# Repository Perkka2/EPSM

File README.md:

# EPSM
 NES Expansion Port Sound Module (Earlier: Expansion Port Sound Generator)

### An expansion sound card for the Nintendo Entertainment System

It uses an Yamaha YMF288 Soundchip that gives a lot of new audio capabilities to the NES.

## Features of YMF288:
* 3 Pulse Channels with Envelope and Noise
* 6 4OP FM Channels with hard panning stereo.
* 6 Rythm channels featuring 6 different ADPCM Drum Recordings with Hard Panning Stereo support
* 2 Timed IRQ's
## Added features of the EPSM
* Forwards expansion audio from supported gamecarts
  * Original Famicom expansion audio games with compatible adapter
  * PowerPak
  * EverDrive N8
  * EverDrive N8 Pro
  * Other carts using EXP2, EXP6 or EXP9 to output audio
* Alternative 3.5mm jack for Stereo output
  * EPSM Audio forwarding to the NES RCA/RF outputs are disabled when the 3.5mm jack is plugged in
  * NES Audio and Cart Expansion audio plays as Dual Mono on the 3.5mm jack.

## Tools
* Mesen-X: Supports playback of EPSM using any mapper.
* FamiStudio: Allows for music creation for the EPSM and has both ROM and NSF export options.

## Usage
* [Addressing](Docs/Addressing.md)
* [Addressing Fiskbit's Fallback Handler](Docs/Fiskbit-FallbackHandler.md)
* [NESDev wiki](https://www.nesdev.org/wiki/Expansion_Port_Sound_Module)
* [N8 Pro Mappers with EPSM Addressing](Files/N8ProEPSM.zip)

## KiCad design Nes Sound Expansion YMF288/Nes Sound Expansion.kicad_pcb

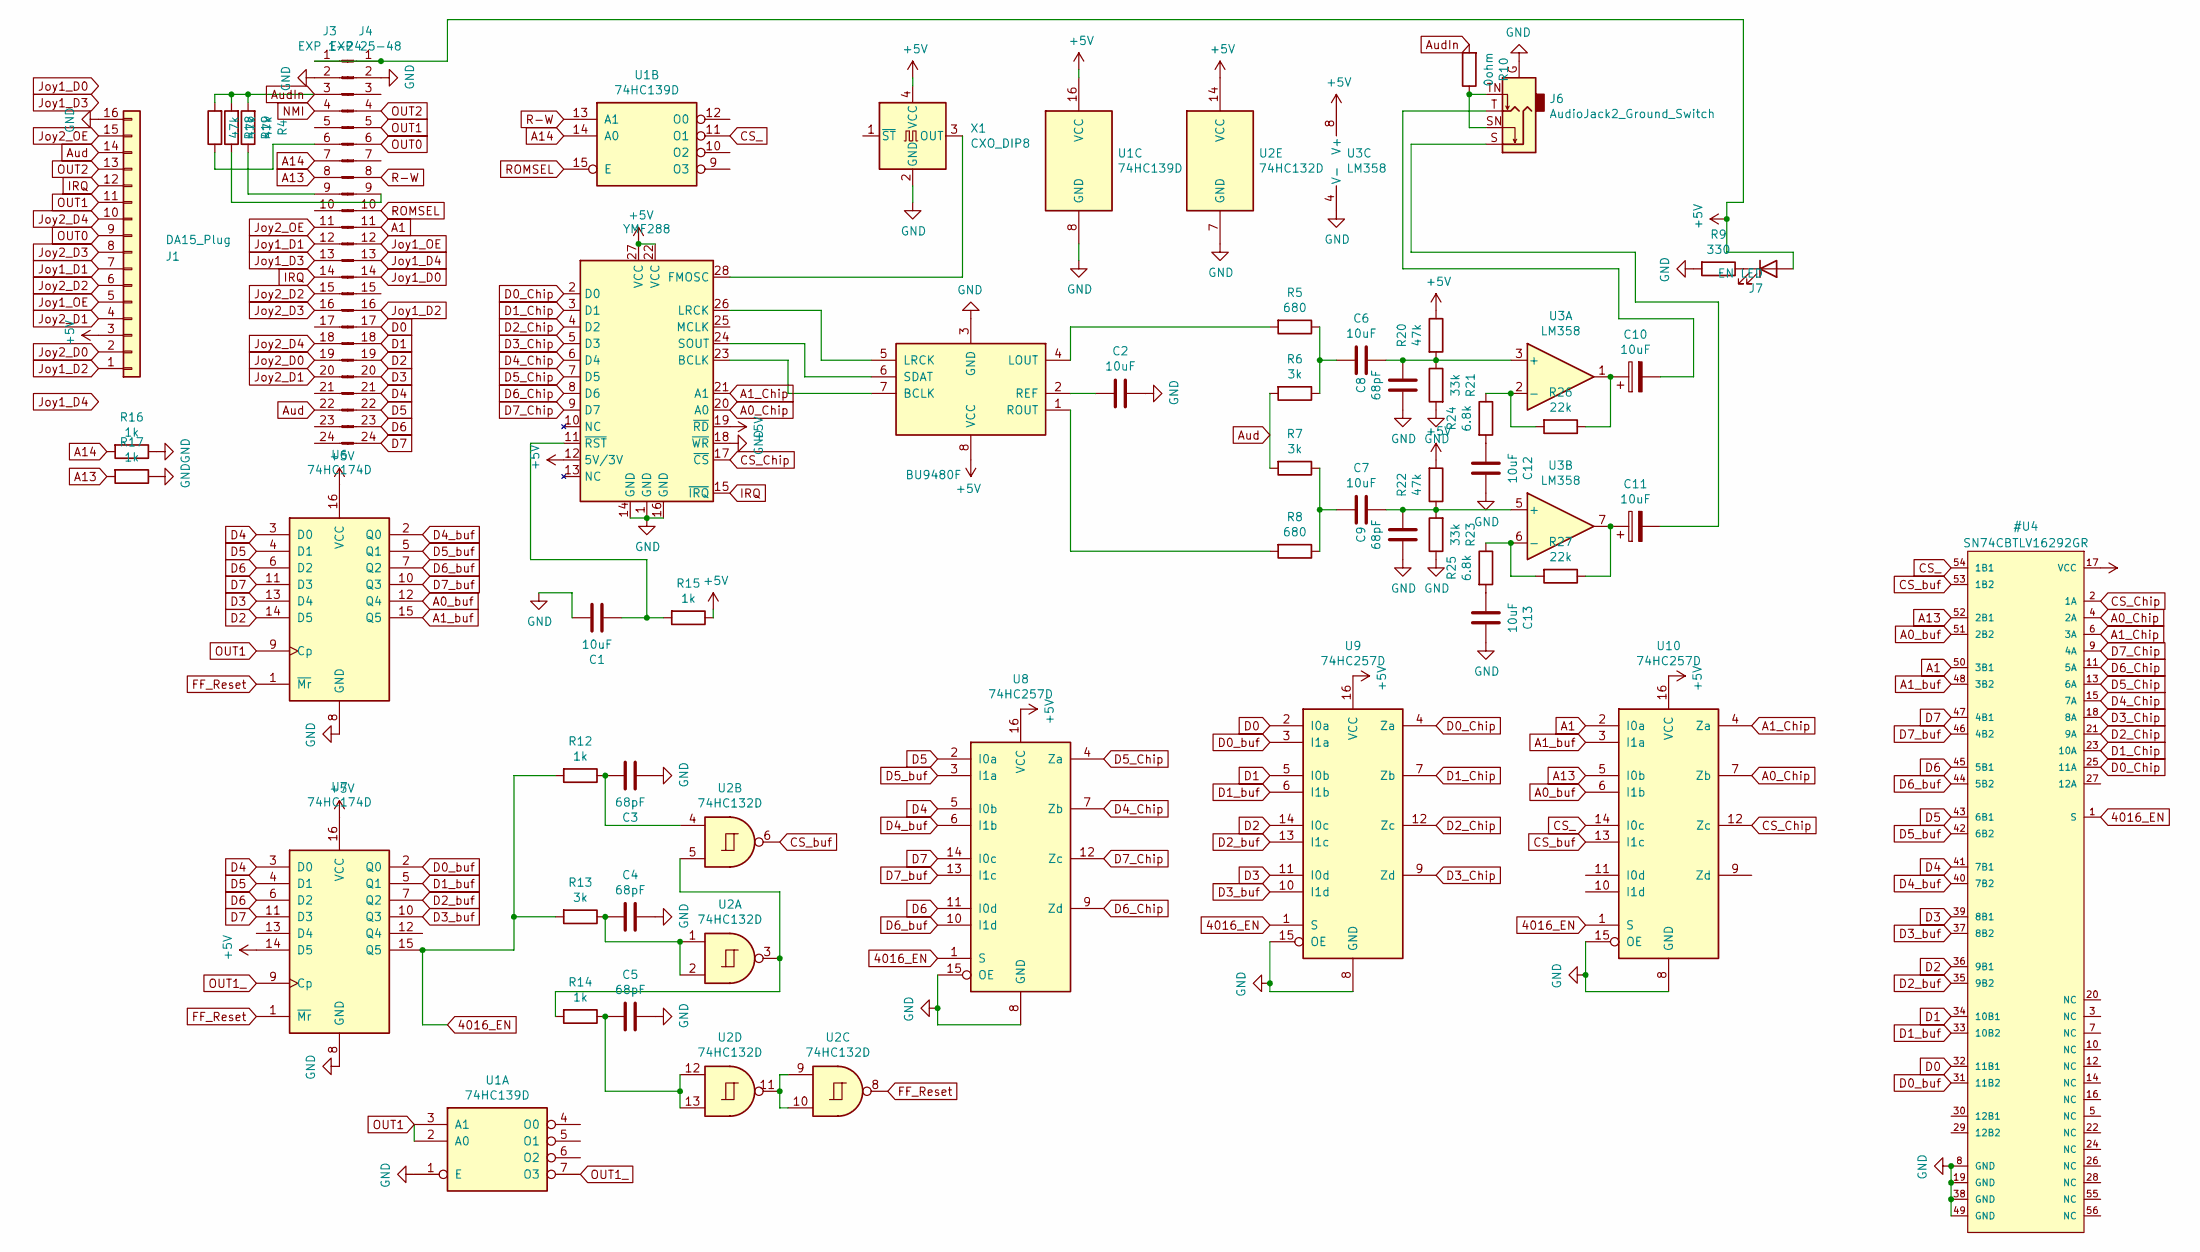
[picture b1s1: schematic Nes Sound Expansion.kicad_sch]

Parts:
BU9480F1: BU9480F; SOIC-8_3.9x4.9mm_P1.27mm
C1, C2, C6, C7, C12, C13: 10uF; C_0805_2012Metric
C3, C4, C5, C8, C9: 68pF; C_0603_1608Metric
C10, C11: 10uF; CP_Elec_4x5.3
J1: DA15_Plug; IDC-Header_2x08_P2.54mm_Vertical
J3: EXP 1-24; PinHeader_1x24_P2.54mm_Vertical
J4: EXP 25-48; PinHeader_1x24_P2.54mm_Vertical
J6: AudioJack2_Ground_Switch; Jack_3.5mm_PJ311_Horizontal_other_pinout
J7: EN LED; LED_0805_2012Metric
R4, R18, R19, R20, R22: 47k; R_0603_1608Metric
R5, R8: 680; R_0603_1608Metric
R6, R7, R13: 3k; R_0603_1608Metric
R9: 330; R_0603_1608Metric
R10: 0ohm; R_0603_1608Metric
R12, R14, R15, R16, R17: 1k; R_0603_1608Metric
R21, R23: 33k; R_0603_1608Metric
R24, R25: 6.8k; R_0603_1608Metric
R26, R27: 22k; R_0603_1608Metric
U1: 74HC139D; SOIC-16_3.9x9.9mm_P1.27mm
U2: 74HC132D; SOIC-14_3.9x8.7mm_P1.27mm
U3: LM358; SOIC-8_3.9x4.9mm_P1.27mm
U6, U7: 74HC174D; SOIC-16_3.9x9.9mm_P1.27mm
U8, U9, U10: 74HC257D; SOIC-16_3.9x9.9mm_P1.27mm
X1: CXO_DIP8; Oscillator_SMD_SeikoEpson_SG8002LB-4Pin_5.0x3.2mm
YMF288: YMF288

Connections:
A14: J3.7, R16.2, U1.14 (A0)
Aud: J1.14, J3.22, R6.2, R7.2
AudIn: J3.3, R4.2, R10.2, R18.2, R19.2
FF_Reset: U2.8, U6.1 (~Mr), U7.1 (~Mr)
IRQ: J1.12, J3.14, YMF288.15 (~IRQ)
Joy1_D0: J4.14
Joy1_D1: J1.7, J3.12
Joy1_D2: J1.1, J4.16
Joy1_D3: J3.13
Joy1_D4: J4.13
Joy1_OE: J1.5, J4.12
Joy2_D0: J1.2, J3.19
Joy2_D1: J1.4, J3.20
Joy2_D2: J1.6, J3.15
Joy2_D3: J1.8, J3.16
Joy2_D4: J1.10, J3.18
Joy2_OE: J1.15, J3.11
NMI: J3.4
unnamed: BU9480F1.7 (BCLK), YMF288.23 (BCLK)
unnamed: BU9480F1.4 (LOUT), R5.2
unnamed: BU9480F1.5 (LRCK), YMF288.26 (LRCK)
unnamed: BU9480F1.2 (REF), C2.1
unnamed: BU9480F1.1 (ROUT), R8.2
unnamed: BU9480F1.6 (SDAT), YMF288.24 (SOUT)
unnamed: C3.2, R12.1, U2.4
unnamed: C4.1, R13.1, U2.1, U2.2
unnamed: C5.1, R14.1, U2.12, U2.13
unnamed: C6.1, R5.1, R6.1
unnamed: C7.1, R7.1, R8.1
unnamed: C10.1, R26.1, U3.1
unnamed: C10.2, J6.T
unnamed: C11.1, R27.1, U3.7
unnamed: C11.2, J6.S
unnamed: C12.1, R24.2
unnamed: C13.1, R25.2
unnamed: J3.6, R18.1
unnamed: J3.9, R4.1
unnamed: J4.9, R19.1
unnamed: J6.SN, J6.TN, R10.1
unnamed: J7.1 (K), R9.1
unnamed: R14.2, U2.3, U2.5
unnamed: U2.9, U2.10, U2.11
unnamed: C6.2, C8.1, R20.2, R21.1, U3.3 (+)
unnamed: R24.1, R26.2, U3.2 (-)
unnamed: C7.2, C9.2, R22.1, R23.2, U3.5 (+)
unnamed: R25.1, R27.2, U3.6 (-)
unnamed: X1.3 (OUT), YMF288.28 (FMOSC)
unnamed: C1.1, R15.2, YMF288.11 (~RST)
OUT0: J1.9, J4.6
OUT1: J1.11, J4.5, U1.2 (A0), U1.3 (A1), U6.9 (Cp)
OUT1_: U1.7 (O3), U7.9 (Cp)
OUT2: J1.13, J4.4
R-W: J4.8, U1.13 (A1)
ROMSEL: J4.10, U1.15 (E)

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
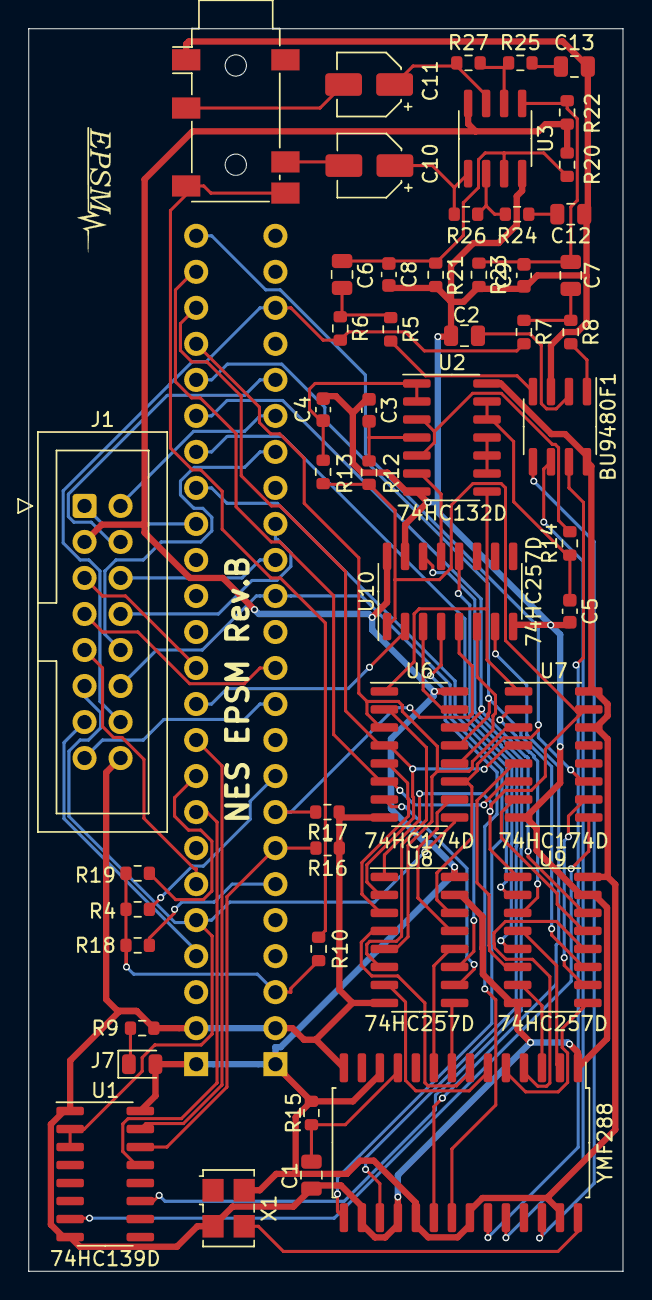
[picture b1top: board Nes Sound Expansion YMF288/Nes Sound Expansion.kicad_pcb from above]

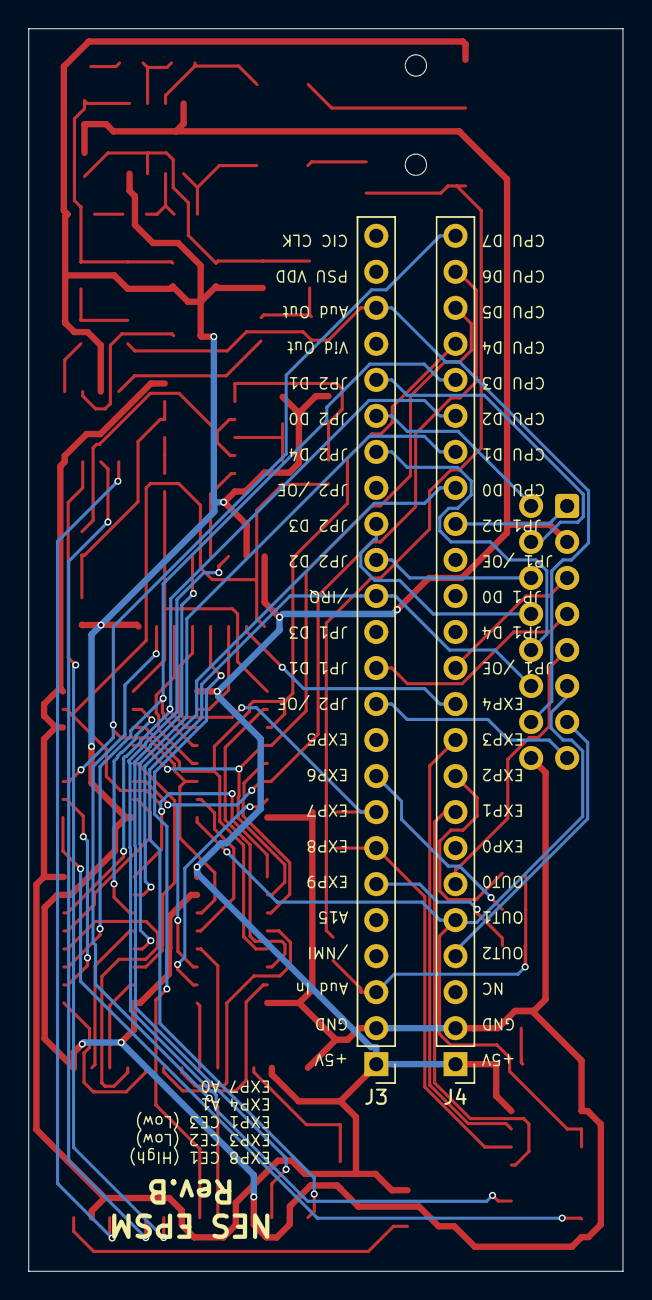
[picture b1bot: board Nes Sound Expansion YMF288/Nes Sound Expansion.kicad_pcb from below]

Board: 2 copper layers, 41.9 x 87.6 mm, 52 parts (2 on the bottom side), 86 nets.

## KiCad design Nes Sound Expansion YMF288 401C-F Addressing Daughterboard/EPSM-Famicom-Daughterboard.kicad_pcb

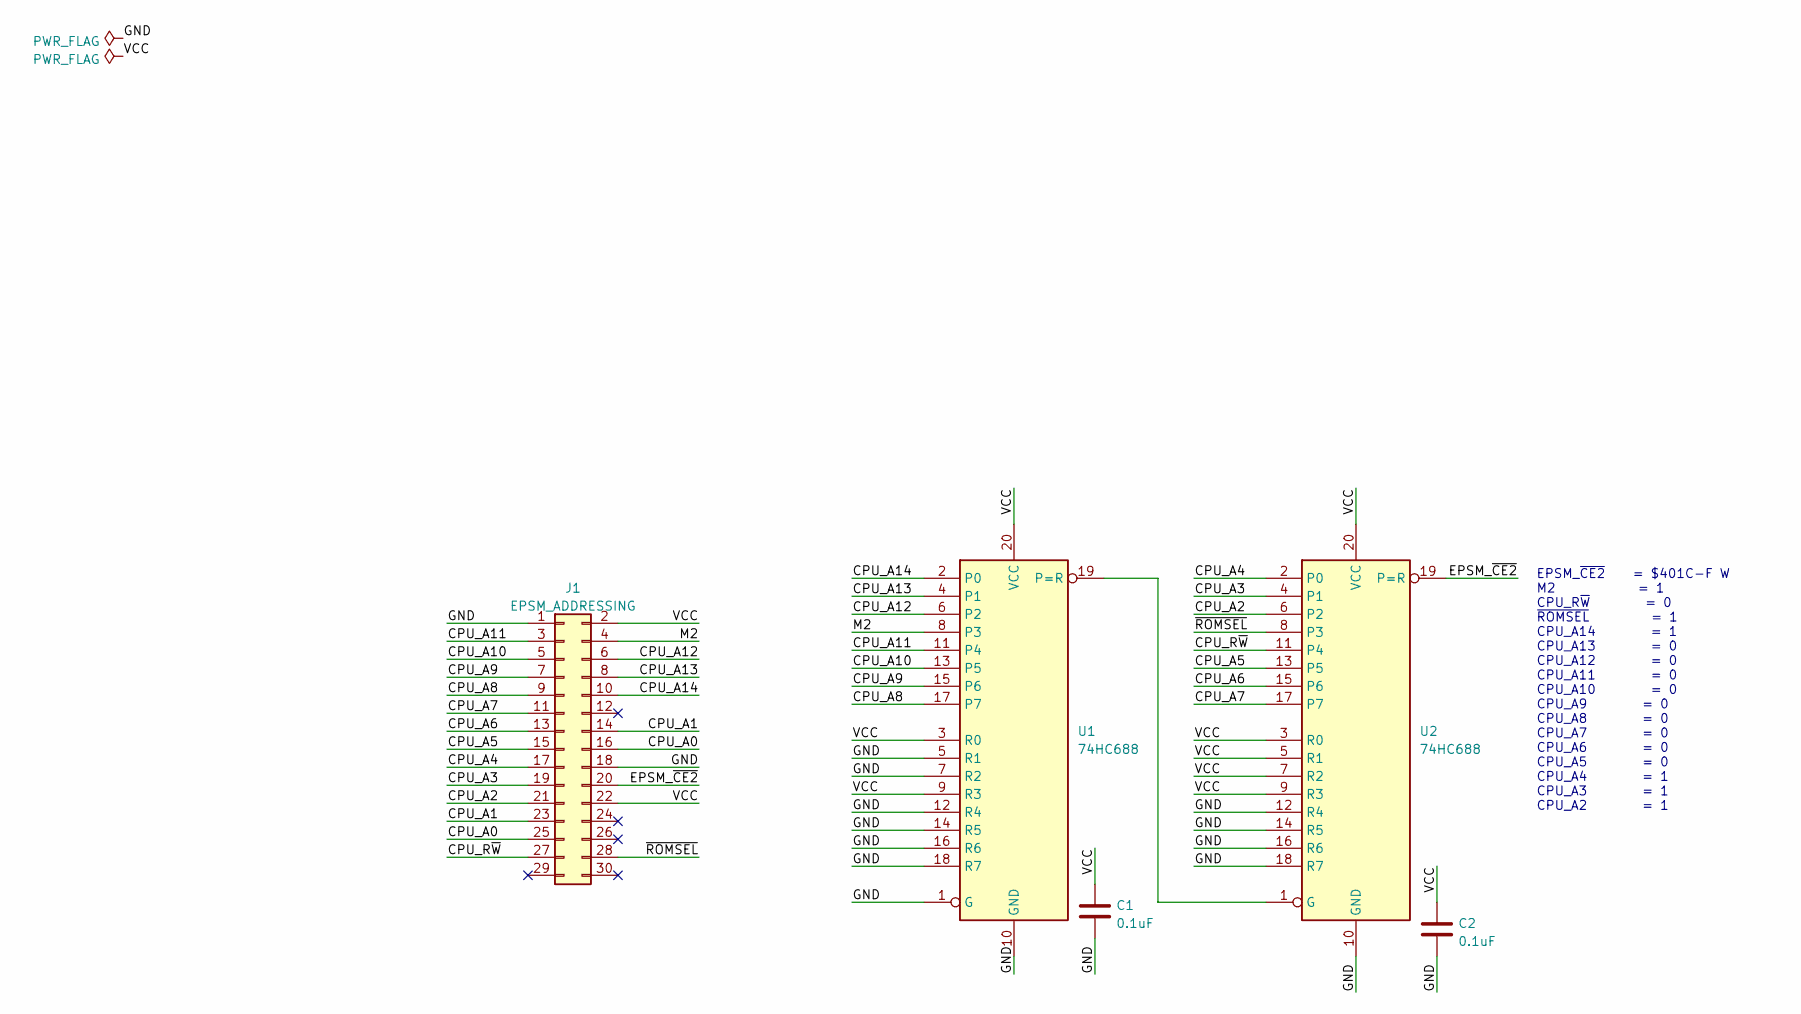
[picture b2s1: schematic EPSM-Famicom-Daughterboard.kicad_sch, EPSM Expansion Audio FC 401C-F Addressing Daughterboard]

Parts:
C1, C2: 0.1uF; C_0805_2012Metric_Pad1.18x1.45mm_HandSolder
J1: EPSM_ADDRESSING; PinHeader_2x15_P2.54mm_Vertical
U1, U2: 74HC688; SOIC-20W_7.5x12.8mm_P1.27mm

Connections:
/CPU_A0: J1.16, J1.25
/CPU_A1: J1.14, J1.23
/CPU_A2: J1.21, U2.6 (P2)
/CPU_A3: J1.19, U2.4 (P1)
/CPU_A4: J1.17, U2.2 (P0)
/CPU_A5: J1.15, U2.13 (P5)
/CPU_A6: J1.13, U2.15 (P6)
/CPU_A7: J1.11, U2.17 (P7)
/CPU_A8: J1.9, U1.17 (P7)
/CPU_A9: J1.7, U1.15 (P6)
/CPU_A10: J1.5, U1.13 (P5)
/CPU_A11: J1.3, U1.11 (P4)
/CPU_A12: J1.6, U1.6 (P2)
/CPU_A13: J1.8, U1.4 (P1)
/CPU_A14: J1.10, U1.2 (P0)
/CPU_R~W: J1.27, U2.11 (P4)
/EPSM_~CE2: J1.20, U2.19 (P=R)
/GND: C1.1, C2.1, J1.1, J1.18, U1.1 (G), U1.5 (R1), U1.7 (R2), U1.10 (GND), U1.12 (R4), U1.14 (R5), U1.16 (R6), U1.18 (R7), U2.10 (GND), U2.12 (R4), U2.14 (R5), U2.16 (R6), U2.18 (R7)
/M2: J1.4, U1.8 (P3)
/VCC: C1.2, C2.2, J1.2, J1.22, U1.3 (R0), U1.9 (R3), U1.20 (VCC), U2.3 (R0), U2.5 (R1), U2.7 (R2), U2.9 (R3), U2.20 (VCC)
/~ROMSEL: J1.28, U2.8 (P3)
unnamed: U1.19 (P=R), U2.1 (G)

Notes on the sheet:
EPSM_~{CE2} = $401C-F W M2 = 1 CPU_R~{W} = 0 ~{ROMSEL} = 1 CPU_A14 = 1 CPU_A13 = 0 CPU_A12 = 0 CPU_A11 = 0 CPU_A10 = 0 CPU_A9 = 0 CPU_A8 = 0 CPU_A7 = 0 CPU_A6 = 0 CPU_A5 = 0 CPU_A4 = 1 CPU_A3 = 1 CPU_A2 = 1

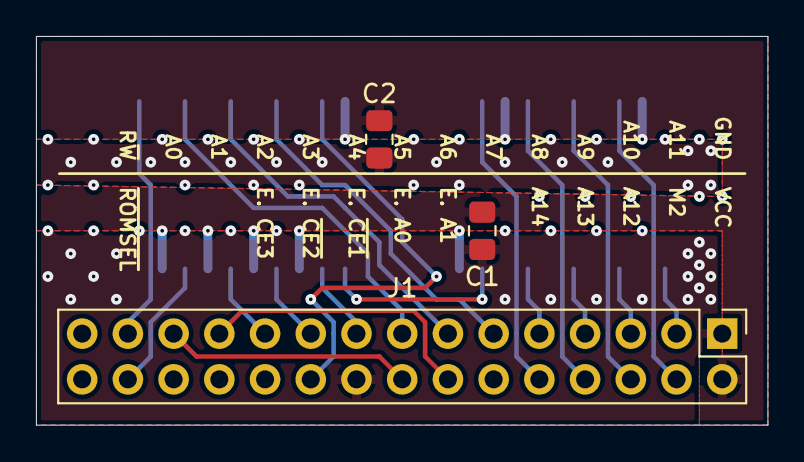
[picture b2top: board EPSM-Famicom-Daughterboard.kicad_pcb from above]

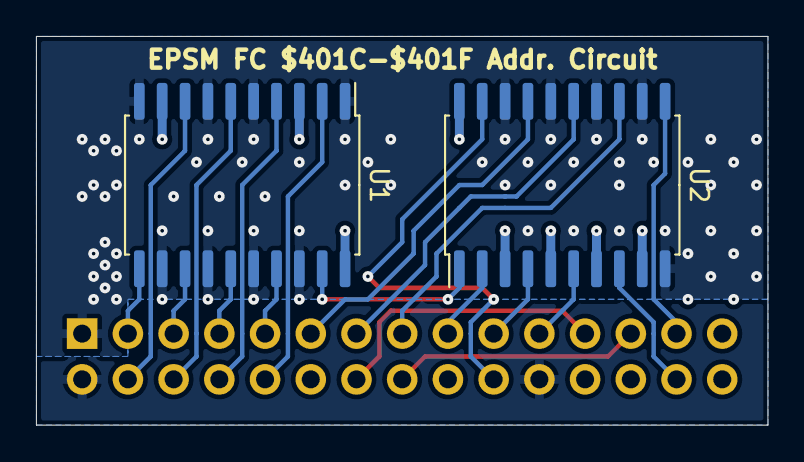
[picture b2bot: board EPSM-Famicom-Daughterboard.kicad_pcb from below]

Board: 2 copper layers, 40.6 x 21.6 mm, 5 parts (2 on the bottom side), 22 nets.

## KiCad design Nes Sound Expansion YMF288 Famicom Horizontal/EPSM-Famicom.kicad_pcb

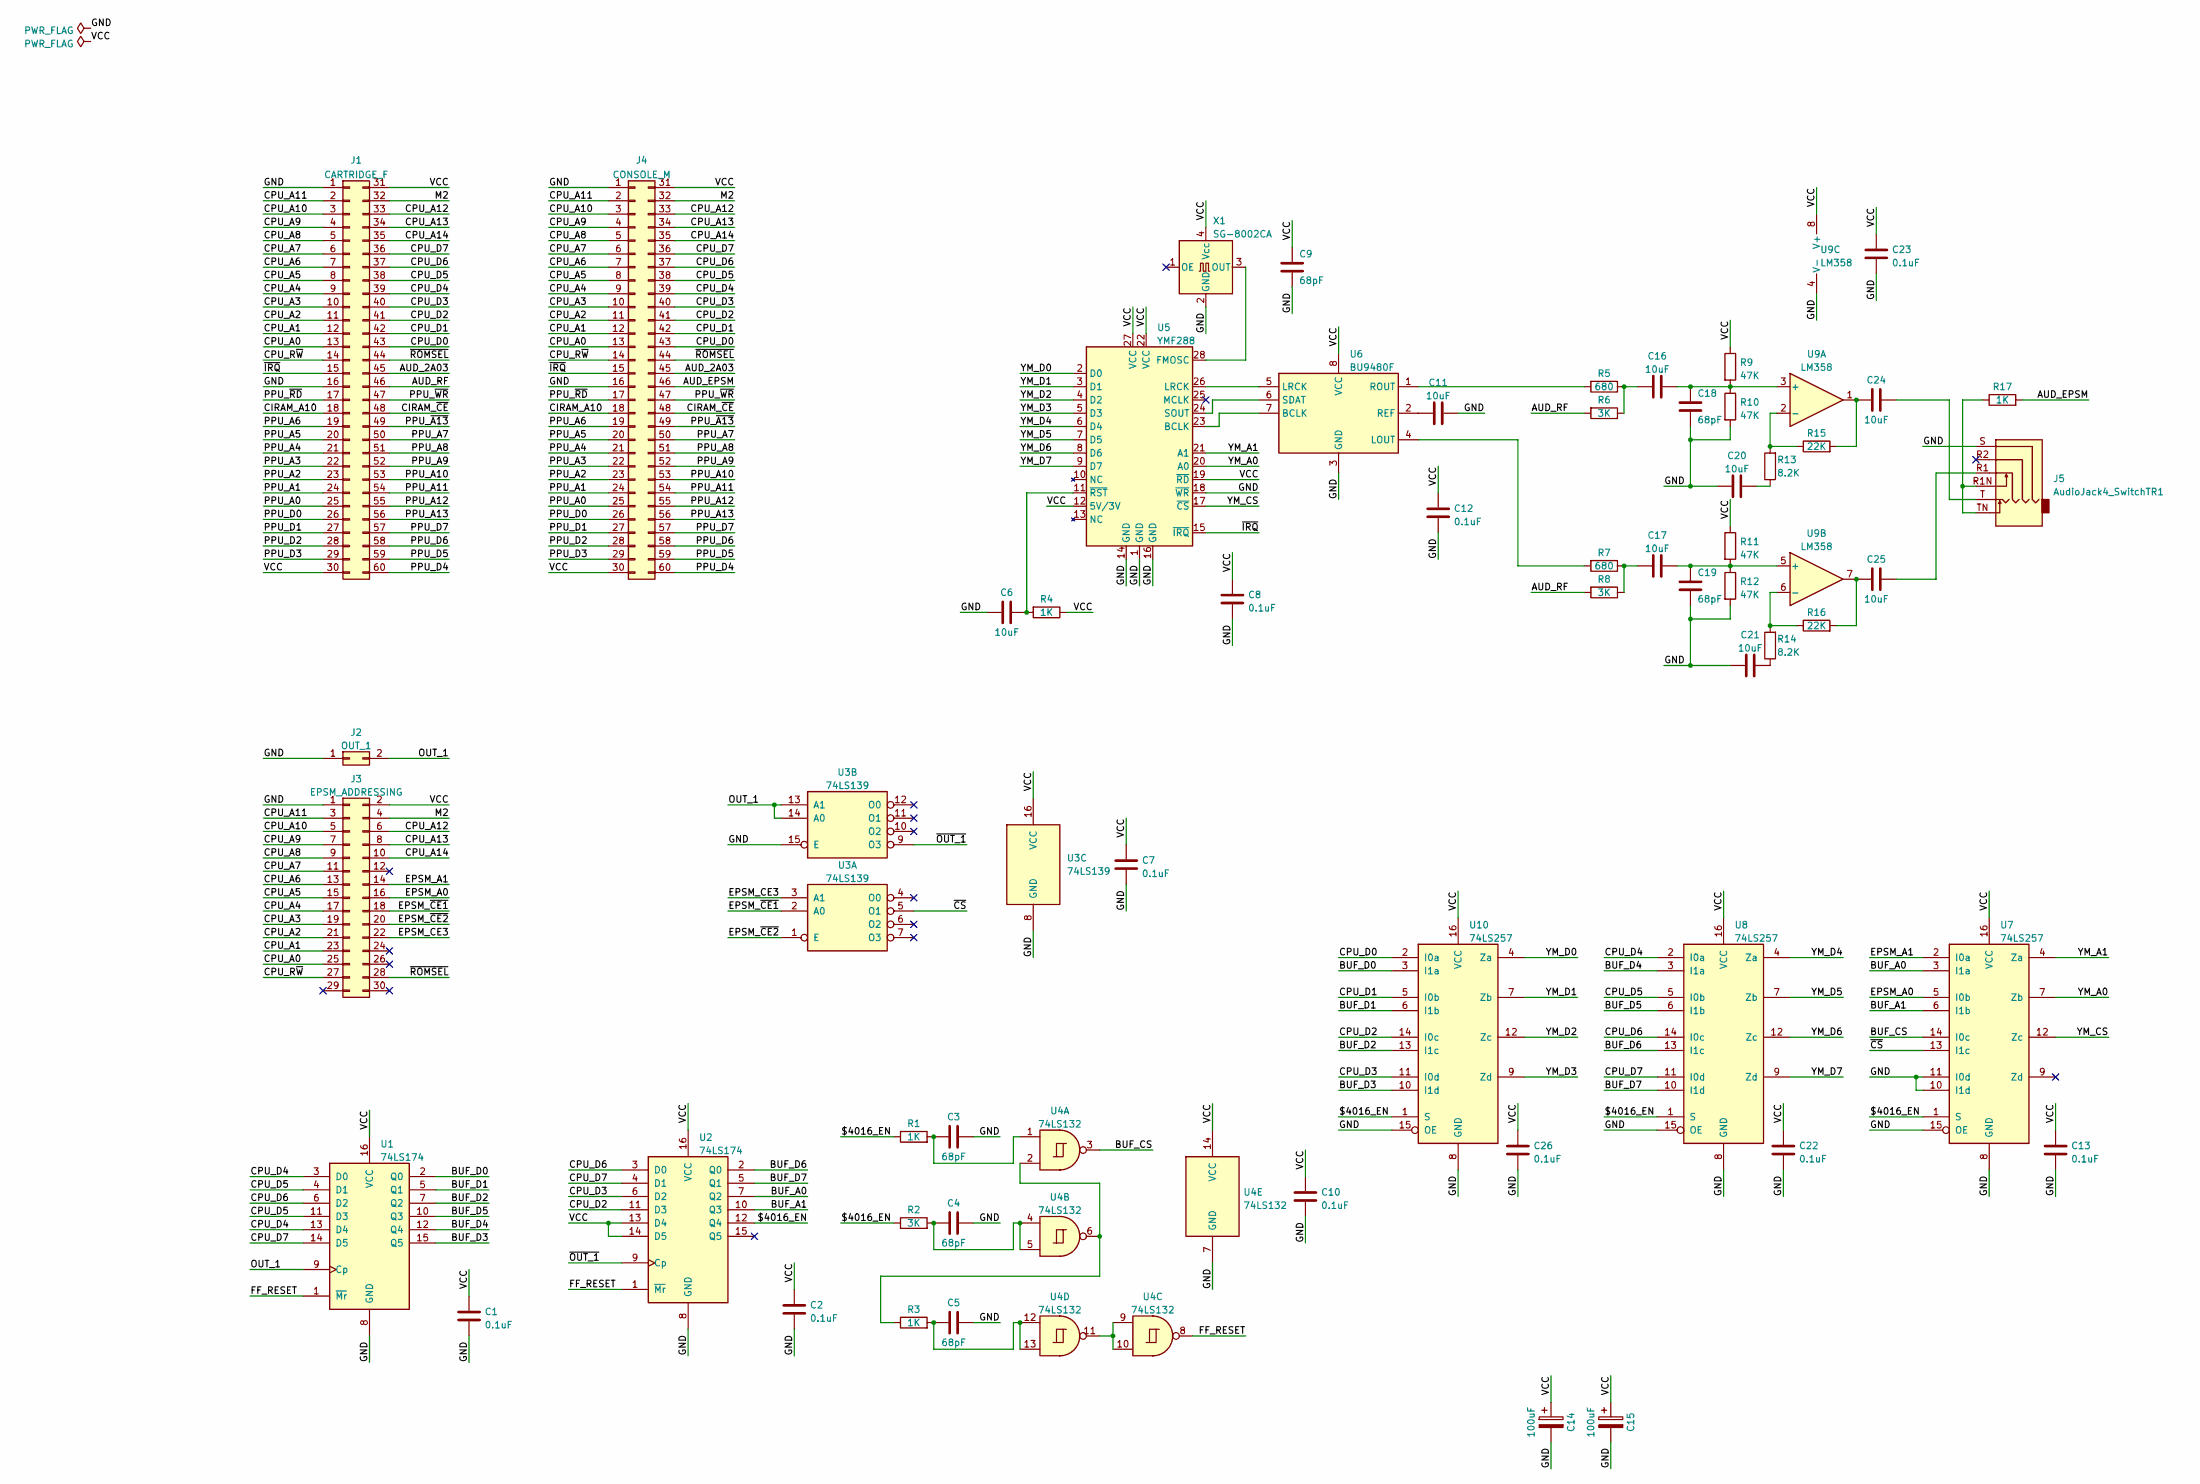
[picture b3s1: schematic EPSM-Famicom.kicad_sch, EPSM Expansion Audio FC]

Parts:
C1, C2, C7, C8, C10, C12, C13, C22, C23, C26: 0.1uF; C_0805_2012Metric_Pad1.18x1.45mm_HandSolder
C3, C4, C5, C9, C18, C19: 68pF; C_0805_2012Metric_Pad1.18x1.45mm_HandSolder
C6, C11, C16, C17, C20, C21, C24, C25: 10uF; C_0805_2012Metric_Pad1.18x1.45mm_HandSolder
C14, C15: 100uF; CP_Radial_D5.0mm_P2.50mm
J1: CARTRIDGE_F; FC_CONN_F
J2: OUT_1; PinHeader_1x02_P2.54mm_Vertical
J3: EPSM_ADDRESSING; PinSocket_2x15_P2.54mm_Vertical_SMD
J4: CONSOLE_M; HVC-ETROM-01
J5: AudioJack4_SwitchTR1; Jack_3.5mm_PJ311_Horizontal
R1, R3, R4, R17: 1K; R_0805_2012Metric_Pad1.20x1.40mm_HandSolder
R2, R6, R8: 3K; R_0805_2012Metric_Pad1.20x1.40mm_HandSolder
R5, R7: 680; R_0805_2012Metric_Pad1.20x1.40mm_HandSolder
R9, R10, R11, R12: 47K; R_0805_2012Metric_Pad1.20x1.40mm_HandSolder
R13, R14: 8.2K; R_0805_2012Metric_Pad1.20x1.40mm_HandSolder
R15, R16: 22K; R_0805_2012Metric_Pad1.20x1.40mm_HandSolder
U1, U2: 74LS174; SOIC-16_3.9x9.9mm_P1.27mm
U3: 74LS139; SOIC-16_3.9x9.9mm_P1.27mm
U4: 74LS132; SOIC-14_3.9x8.7mm_P1.27mm
U5: YMF288; SOP-28_7.5x12.8mm_P1.27mm
U6: BU9480F; SOIC-8_5.275x5.275mm_P1.27mm
U7, U8, U10: 74LS257; SOIC-16_3.9x9.9mm_P1.27mm
U9: LM358; SOIC-8_3.9x4.9mm_P1.27mm
X1: SG-8002CA; Oscillator_SMD_SeikoEpson_SG8002LB-4Pin_5.0x3.2mm

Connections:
/$4016_EN: R1.1, R2.1, U2.12 (Q4), U7.1 (S), U8.1 (S), U10.1 (S)
/AUD_2A03: J1.45, J4.45
/AUD_EPSM: J4.46, R17.2
/AUD_RF: J1.46, R6.2, R8.2
/BUF_A0: U2.7 (Q2), U7.3 (I1a)
/BUF_A1: U2.10 (Q3), U7.6 (I1b)
/BUF_CS: U4.3, U7.14 (I0c)
/BUF_D0: U1.2 (Q0), U10.3 (I1a)
/BUF_D1: U1.5 (Q1), U10.6 (I1b)
/BUF_D2: U1.7 (Q2), U10.13 (I1c)
/BUF_D3: U1.15 (Q5), U10.10 (I1d)
/BUF_D4: U1.12 (Q4), U8.3 (I1a)
/BUF_D5: U1.10 (Q3), U8.6 (I1b)
/BUF_D6: U2.2 (Q0), U8.13 (I1c)
/BUF_D7: U2.5 (Q1), U8.10 (I1d)
/CIRAM_A10: J1.18, J4.18
/CIRAM_~CE: J1.48, J4.48
/CPU_A0: J1.13, J3.25, J4.13
/CPU_A1: J1.12, J3.23, J4.12
/CPU_A2: J1.11, J3.21, J4.11
/CPU_A3: J1.10, J3.19, J4.10
/CPU_A4: J1.9, J3.17, J4.9
/CPU_A5: J1.8, J3.15, J4.8
/CPU_A6: J1.7, J3.13, J4.7
/CPU_A7: J1.6, J3.11, J4.6
/CPU_A8: J1.5, J3.9, J4.5
/CPU_A9: J1.4, J3.7, J4.4
/CPU_A10: J1.3, J3.5, J4.3
/CPU_A11: J1.2, J3.3, J4.2
/CPU_A12: J1.33, J3.6, J4.33
/CPU_A13: J1.34, J3.8, J4.34
/CPU_A14: J1.35, J3.10, J4.35
/CPU_D0: J1.43, J4.43, U10.2 (I0a)
/CPU_D1: J1.42, J4.42, U10.5 (I0b)
/CPU_D2: J1.41, J4.41, U2.11 (D3), U10.14 (I0c)
/CPU_D3: J1.40, J4.40, U2.6 (D2), U10.11 (I0d)
/CPU_D4: J1.39, J4.39, U1.3 (D0), U1.13 (D4), U8.2 (I0a)
/CPU_D5: J1.38, J4.38, U1.4 (D1), U1.11 (D3), U8.5 (I0b)
/CPU_D6: J1.37, J4.37, U1.6 (D2), U2.3 (D0), U8.14 (I0c)
/CPU_D7: J1.36, J4.36, U1.14 (D5), U2.4 (D1), U8.11 (I0d)
/CPU_R~W: J1.14, J3.27, J4.14
/EPSM_A0: J3.16, U7.5 (I0b)
/EPSM_A1: J3.14, U7.2 (I0a)
/EPSM_CE3: J3.22, U3.3 (A1)
/EPSM_~CE1: J3.18, U3.2 (A0)
/EPSM_~CE2: J3.20, U3.1 (E)
/FF_RESET: U1.1 (~Mr), U2.1 (~Mr), U4.8
/GND: C1.1, C2.1, C3.2, C4.2, C5.2, C6.1, C7.1, C8.1, C9.2, C10.1, C11.2, C12.1, C13.1, C14.2, C15.2, C18.2, C19.2, C20.1, C21.1, C22.1, C23.1, C26.1, J1.1, J1.16, J2.1, J3.1, J4.1, J4.16, J5.S, R10.2, R12.2, U1.8 (GND), U2.8 (GND), U3.8 (GND), U3.15 (E), U4.7 (GND), U5.1 (GND), U5.14 (GND), U5.16 (GND), U5.18 (~WR), U6.3 (GND), U7.8 (GND), U7.10 (I1d), U7.11 (I0d), U7.15 (OE), U8.8 (GND), U8.15 (OE), U9.4 (V-), U10.8 (GND), U10.15 (OE), X1.2 (GND)
/M2: J1.32, J3.4, J4.32
/OUT_1: J2.2, U1.9 (Cp), U3.13 (A1), U3.14 (A0)
/PPU_A0: J1.25, J4.25
/PPU_A1: J1.24, J4.24
/PPU_A2: J1.23, J4.23
/PPU_A3: J1.22, J4.22
/PPU_A4: J1.21, J4.21
/PPU_A5: J1.20, J4.20
/PPU_A6: J1.19, J4.19
/PPU_A7: J1.50, J4.50
/PPU_A8: J1.51, J4.51
/PPU_A9: J1.52, J4.52
/PPU_A10: J1.53, J4.53
/PPU_A11: J1.54, J4.54
/PPU_A12: J1.55, J4.55
/PPU_A13: J1.56, J4.56
/PPU_D0: J1.26, J4.26
/PPU_D1: J1.27, J4.27
/PPU_D2: J1.28, J4.28
/PPU_D3: J1.29, J4.29
/PPU_D4: J1.60, J4.60
/PPU_D5: J1.59, J4.59
/PPU_D6: J1.58, J4.58
/PPU_D7: J1.57, J4.57
/PPU_~A13: J1.49, J4.49
/PPU_~RD: J1.17, J4.17
/PPU_~WR: J1.47, J4.47
/VCC: C1.2, C2.2, C7.2, C8.2, C9.1, C10.2, C12.2, C13.2, C14.1, C15.1, C22.2, C23.2, C26.2, J1.30, J1.31, J3.2, J4.30, J4.31, R4.1, R9.1, R11.1, U1.16 (VCC), U2.13 (D4), U2.14 (D5), U2.16 (VCC), U3.16 (VCC), U4.14 (VCC), U5.12 (5V/3V), U5.19 (~RD), U5.22 (VCC), U5.27 (VCC), U6.8 (VCC), U7.16 (VCC), U8.16 (VCC), U9.8 (V+), U10.16 (VCC), X1.4 (Vcc)
/YM_A0: U5.20 (A0), U7.7 (Zb)
/YM_A1: U5.21 (A1), U7.4 (Za)
/YM_CS: U5.17 (~CS), U7.12 (Zc)
/YM_D0: U5.2 (D0), U10.4 (Za)
/YM_D1: U5.3 (D1), U10.7 (Zb)
/YM_D2: U5.4 (D2), U10.12 (Zc)
/YM_D3: U5.5 (D3), U10.9 (Zd)
/YM_D4: U5.6 (D4), U8.4 (Za)
/YM_D5: U5.7 (D5), U8.7 (Zb)
/YM_D6: U5.8 (D6), U8.12 (Zc)
/YM_D7: U5.9 (D7), U8.9 (Zd)
/~CS: U3.5 (O1), U7.13 (I1c)
/~IRQ: J1.15, J4.15, U5.15 (~IRQ)
/~OUT_1: U2.9 (Cp), U3.9 (O3)
/~ROMSEL: J1.44, J3.28, J4.44
unnamed: C3.1, R1.2, U4.1
unnamed: C4.1, R2.2, U4.4, U4.5
unnamed: C5.1, R3.2, U4.12, U4.13
unnamed: C6.2, R4.2, U5.11 (~RST)
unnamed: C11.1, U6.2 (REF)
unnamed: C16.1, R5.1, R6.1
unnamed: C16.2, C18.1, R9.2, R10.1, U9.3 (+)
unnamed: C17.1, R7.1, R8.1
unnamed: C17.2, C19.1, R11.2, R12.1, U9.5 (+)
unnamed: C20.2, R13.1
unnamed: C21.2, R14.1
unnamed: C24.1, R15.2, U9.1
unnamed: C24.2, J5.T
unnamed: C25.1, R16.2, U9.7
unnamed: C25.2, J5.R1
unnamed: J5.R1N, J5.TN, R17.1
unnamed: R3.1, U4.2, U4.6
unnamed: R5.2, U6.1 (ROUT)
unnamed: R7.2, U6.4 (LOUT)
unnamed: R13.2, R15.1, U9.2 (-)
unnamed: R14.2, R16.1, U9.6 (-)
unnamed: U4.9, U4.10, U4.11
unnamed: U5.23 (BCLK), U6.7 (BCLK)
unnamed: U5.24 (SOUT), U6.6 (SDAT)
unnamed: U5.26 (LRCK), U6.5 (LRCK)
unnamed: U5.28 (FMOSC), X1.3 (OUT)

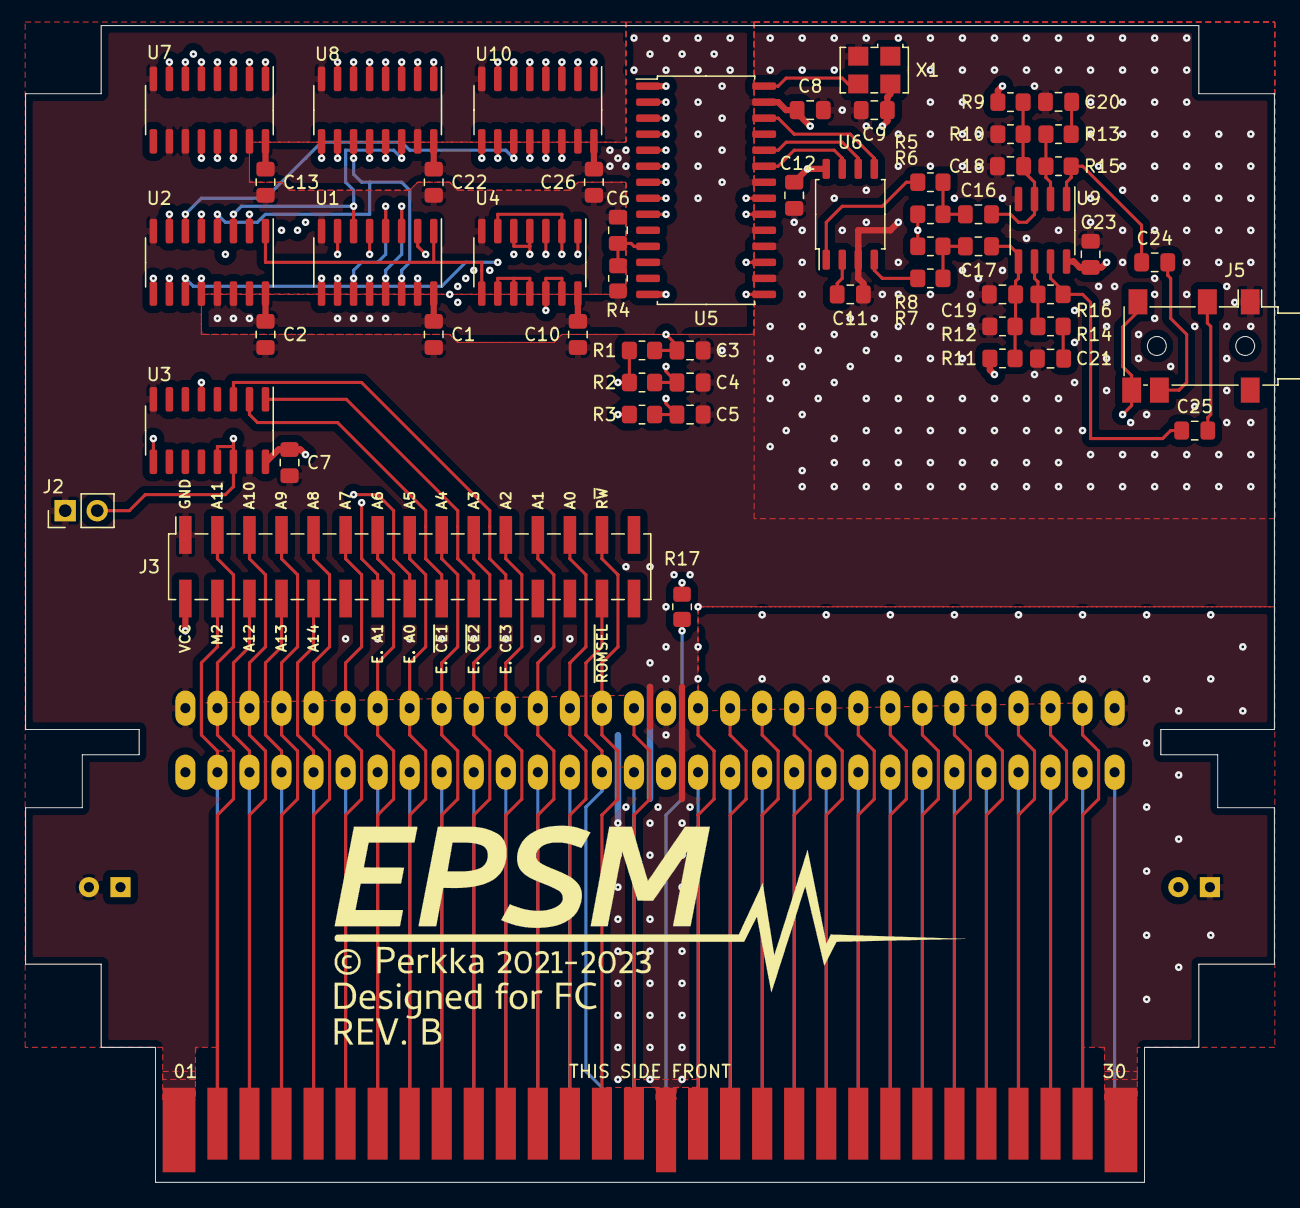
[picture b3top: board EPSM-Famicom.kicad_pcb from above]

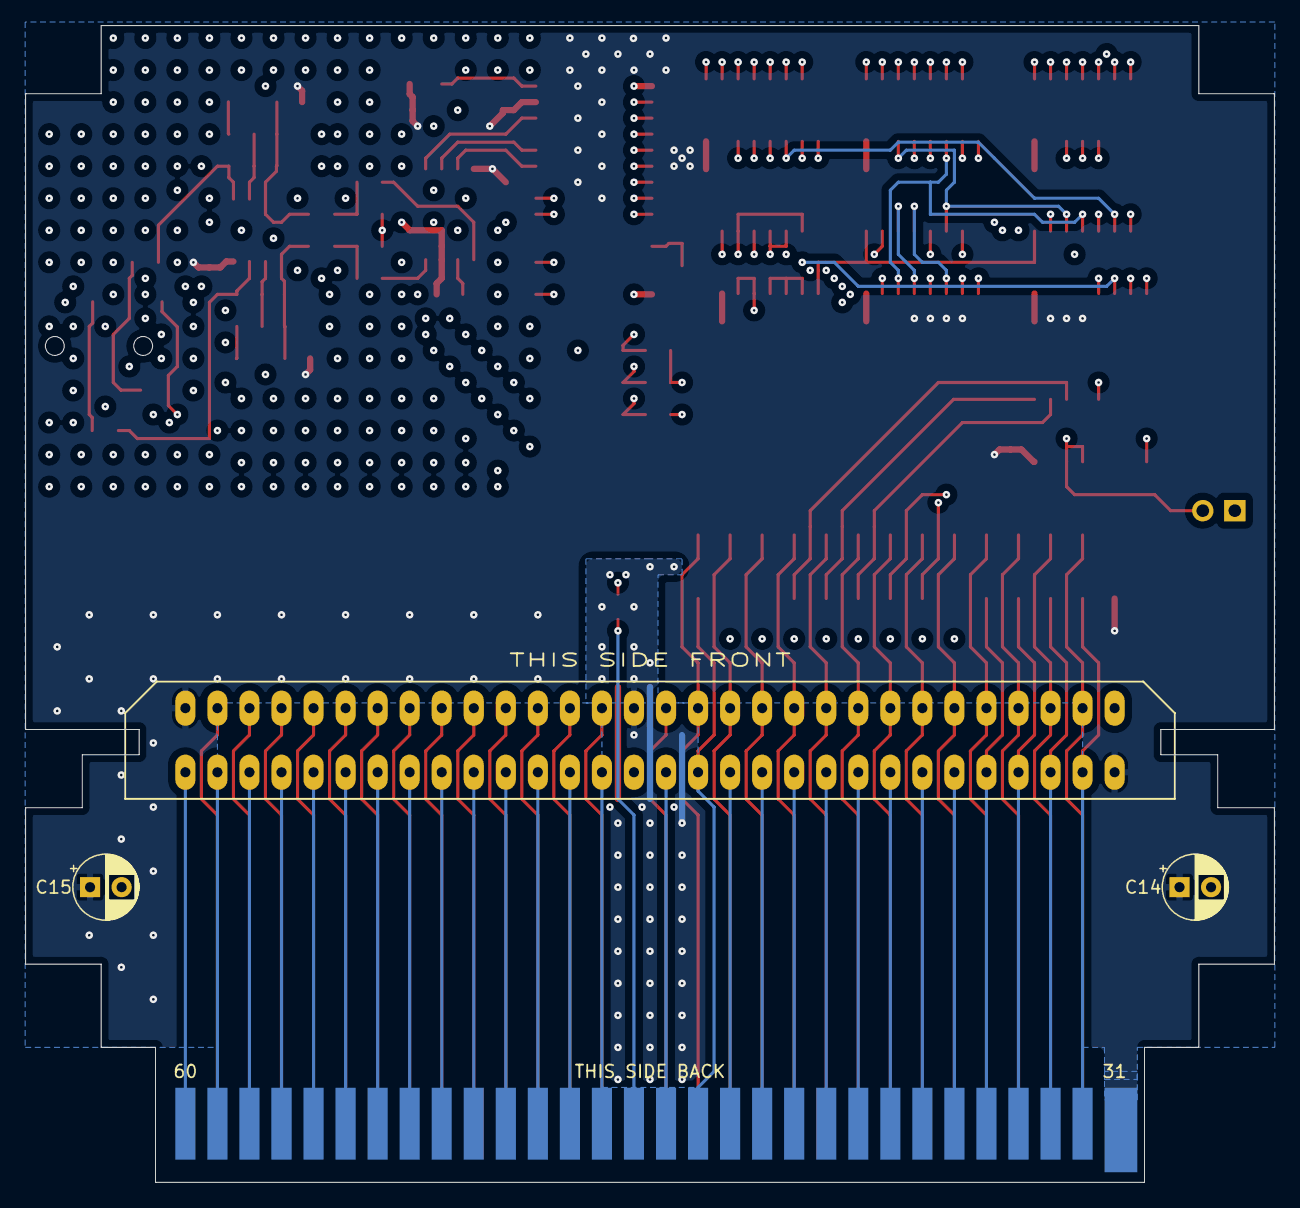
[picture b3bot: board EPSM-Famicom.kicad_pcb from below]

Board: 4 copper layers, 99.0 x 91.7 mm, 60 parts (3 on the bottom side), 117 nets.

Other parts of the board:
Ref**: Val**; EPSM_silkscreen
